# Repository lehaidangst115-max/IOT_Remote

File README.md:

Remote có thể gửi đáp án A, B, C, D bằng nút xác nhận đến MQTT.
Web sẽ subscribe vào topic class/quiz/answer để nhận câu trả lời từ remote theo cú pháp
{
  "block_id": "33",
  "stt": 2,
  "answer": "B"
}

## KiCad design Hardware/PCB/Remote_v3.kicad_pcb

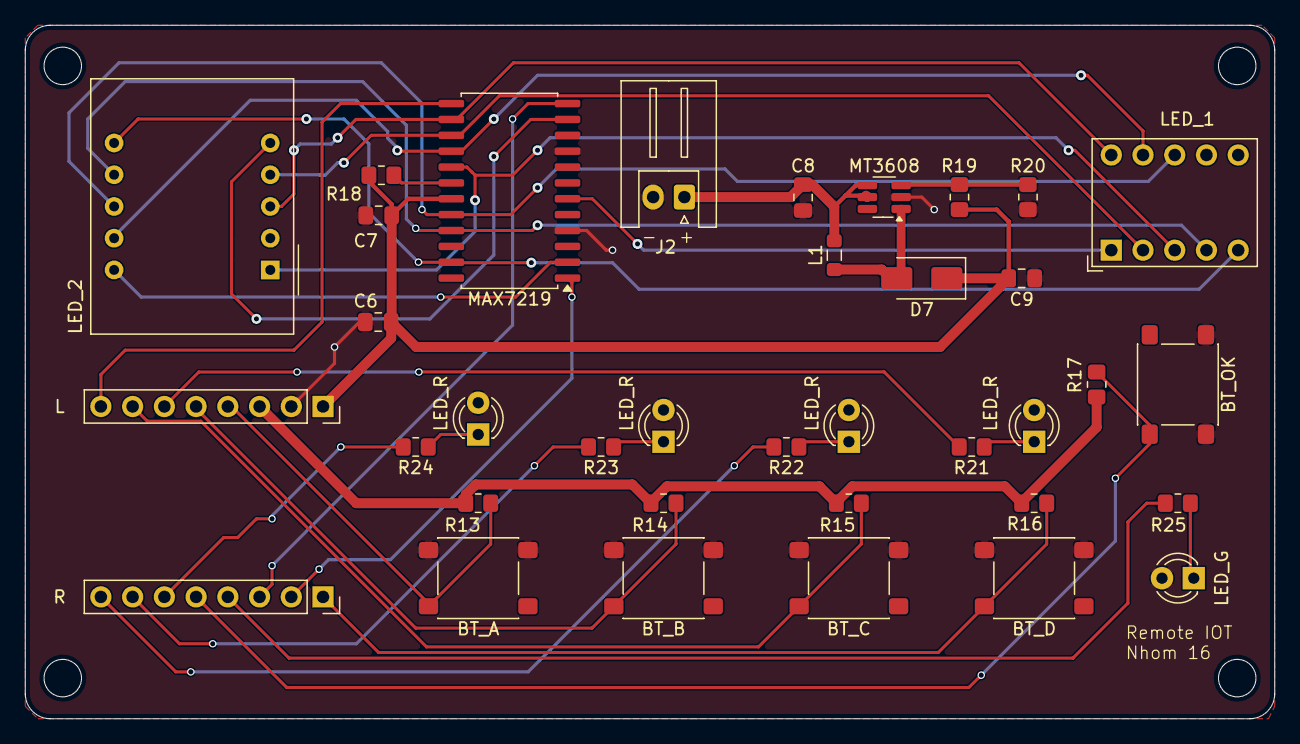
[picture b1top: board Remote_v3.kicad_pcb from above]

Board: 2 copper layers, 100.0 x 55.5 mm, 36 parts (0 on the bottom side), 35 nets.

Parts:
BT_A: BT_A; SW_SPST_PTS645Sx43SMTR92
BT_B: SW_Push; SW_SPST_PTS645Sx43SMTR92
BT_C: SW_Push; SW_SPST_PTS645Sx43SMTR92
BT_D: SW_Push; SW_SPST_PTS645Sx43SMTR92
BT_OK: SW_Push; SW_SPST_PTS645Sx43SMTR92
C6: 10uF; C_0805_2012Metric_Pad1.18x1.45mm_HandSolder
C7: 100nF; C_0805_2012Metric_Pad1.18x1.45mm_HandSolder
C8, C9: 22uF; C_0805_2012Metric_Pad1.18x1.45mm_HandSolder
D7: SS14; D_SMA
J2: Conn_01x02; JST_XH_S2B-XH-A_1x02_P2.50mm_Horizontal
L: J_LEFT; PinSocket_1x08_P2.54mm_Vertical
L1: 4.7uH; L_0805_2012Metric_Pad1.05x1.20mm_HandSolder
LED_1: SC39-12GWA; Sx39-1xxxxx
LED_2: ELD-426SYGWA; ELD_426XXXX
LED_G: LED_OK; LED_D3.0mm_Clear
LED_R: LED_A; LED_D3.0mm_Clear
LED_R#2: LED_B; LED_D3.0mm_Clear
LED_R#3: LED_C; LED_D3.0mm_Clear
LED_R#4: LED_D; LED_D3.0mm_Clear
MAX7219: MAX7219; SOIC-24W_7.5x15.4mm_P1.27mm
MT3608: MT3608; SOT-23-6_Handsoldering
R: J_RIGHT; PinSocket_1x08_P2.54mm_Vertical
R13, R14, R15, R16, R17, R18, R20: 10K; R_0805_2012Metric_Pad1.20x1.40mm_HandSolder
R19: 75K; R_0805_2012Metric_Pad1.20x1.40mm_HandSolder
R21, R22, R23, R24: 330; R_0805_2012Metric_Pad1.20x1.40mm_HandSolder
R25: 150; R_0805_2012Metric_Pad1.20x1.40mm_HandSolder

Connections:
BAT+: C8.2, J2.1, L1.1, MT3608.4 (EN), MT3608.5 (IN)
BT_A: BT_A.1, L.4, R13.1
BT_B: BT_B.1, L.5, R14.1
BT_C: BT_C.1, L.7, R15.1
BT_D: BT_D.1, R.1, R16.1
BT_OK: BT_OK.2, R.5, R17.1
DIG_0: LED_2.10 (CA_D1), MAX7219.2 (DIG_0)
DIG_1: LED_2.5 (CA_D2), MAX7219.11 (DIG_1)
DIG_2: LED_1.1 (CC), MAX7219.6 (DIG_2)
GND: BT_A.2, BT_B.2, BT_C.2, BT_D.2, BT_OK.1, C6.1, C7.1, C8.1, C9.1, J2.2, L.2, LED_G.2 (A), LED_R.2 (A), LED_R#2.2 (A), LED_R#3.2 (A), LED_R#4.2 (A), MAX7219.4 (GND), MAX7219.9 (GND), MT3608.2 (GND), R20.1
MAX_CLK: L.8, MAX7219.13 (CLK)
MAX_CS: MAX7219.12 (LOAD), R.3
MAX_DIN: MAX7219.1 (DIN), R.2
unnamed: LED_R#4.1 (K), R21.1
unnamed: LED_R#3.1 (K), R22.1
unnamed: LED_R#2.1 (K), R23.1
unnamed: LED_R.1 (K), R24.1
unnamed: LED_G.1 (K), R25.1
unnamed: D7.2 (A), L1.2, MT3608.1 (SW)
unnamed: L.6, R21.2
unnamed: R.4, R25.2
unnamed: R.6, R24.2
unnamed: R.7, R23.2
unnamed: R.8, R22.2
unnamed: MAX7219.18 (ISET), R18.2
unnamed: MT3608.3 (FB), R19.2, R20.2
SEG_A: LED_1.10 (A), LED_2.3 (e), MAX7219.14 (SEG_A)
SEG_B: LED_1.9 (B), LED_2.9 (g), MAX7219.16 (SEG_B)
SEG_C: LED_1.8 (C), LED_2.8 (f), MAX7219.20 (SEG_C)
SEG_D: LED_1.5 (D), LED_2.6 (b), MAX7219.23 (SEG_D)
SEG_E: LED_1.4 (E), LED_2.7 (a), MAX7219.21 (SEG_E)
SEG_F: LED_1.2 (F), LED_2.4 (c), MAX7219.15 (SEG_F)
SEG_G: LED_1.3 (G), LED_2.1 (d), MAX7219.17 (SEG_G)
VCC_3V3: L.3, R13.2, R14.2, R15.2, R16.2, R17.2
VCC_5V: C6.2, C7.2, C9.2, D7.1 (K), L.1, MAX7219.19 (V+), R18.1, R19.1
